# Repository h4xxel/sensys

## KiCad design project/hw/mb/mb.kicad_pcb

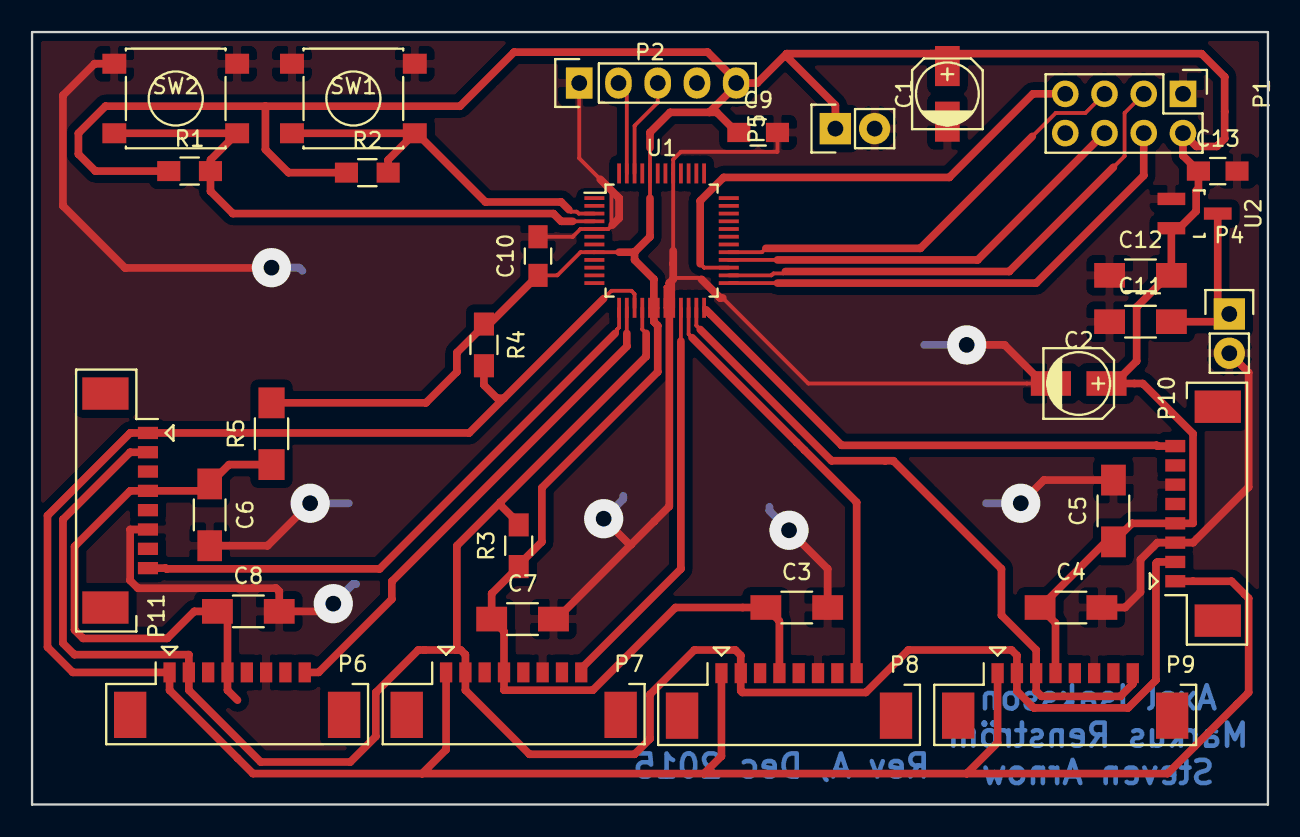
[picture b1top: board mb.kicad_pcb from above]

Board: 2 copper layers, 80.0 x 50.0 mm, 32 parts (0 on the bottom side), 20 nets.

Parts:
C1, C2: CP; c_elec_4x5.7
C3, C4, C5, C6, C7, C8, C11, C12: 1u; C_1206_HandSoldering
C9, C10, C13: 100n; C_0805_HandSoldering
P1: CONN_02X04; Pin_Header_Straight_2x04
P2: CONN_01X05; Pin_Header_Straight_1x05
P4, P5: CONN_01X02; Pin_Header_Straight_1x02
P6, P7, P8, P9, P10, P11: CONN_01X08; Connector_Molex_PicoBlade_53398-0871
R1, R2: R; R_0805_HandSoldering
R3, R4: 4k7; R_0805_HandSoldering
R5: 0; R_1206_HandSoldering
SW1, SW2: SW_PUSH; SW_SPST_PTS645
U1: LPC1114/302; TQFP-48_7x7mm_Pitch0.5mm
U2: mcp1700; SOT-23_Handsoldering

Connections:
+3V3: C1.1, C2.1, C3.1, C4.1, C5.1, C6.1, C7.1, C8.1, C9.1, C10.1, C12.2, C13.1, P1.2, P2.5, P5.1, P6.4, P7.4, P8.4, P9.4, P10.4, P11.4, R1.1, R2.1, R3.1, R4.1, R5.1, R5.2, U1.8, U1.17, U1.18, U1.44, U2.2
/IMUA0: P6.8, U1.14
/IMUA1: P7.8, U1.21
/IMUA2: P8.8, U1.22
/IMUA3: P9.3, P9.8, U1.23
/IMUA4: P10.8, U1.24
/IMUA5: P11.8, U1.13
/MISO: P1.7, U1.27
/MOSI: P1.6, U1.28
/RADIO_CE: P1.3, U1.26
/RADIO_CSN: P1.4, U1.25
/RX: P2.3, U1.46
/SCK: P1.5, U1.29
/SCL: P6.1, P7.1, P8.1, P9.1, P10.1, P11.1, R4.2, U1.15
/SDA: P6.2, P7.2, P8.2, P9.2, P10.2, P11.2, R3.2, U1.16
/TX: P2.2, U1.47
GND: C1.2, C2.2, C3.2, C4.2, C5.2, C6.2, C7.2, C8.2, C9.2, C10.2, C11.1, C12.1, C13.2, P1.1, P2.1, P4.2, P5.2, P6.6, P7.6, P8.6, P9.6, P10.3, P10.6, P11.6, SW1.1, SW2.1, U1.5, U1.19, U1.20, U1.41, U2.1
unnamed: C11.2, P4.1, U2.3
unnamed: R1.2, SW2.2, U1.4
unnamed: R2.2, SW1.2, U1.3

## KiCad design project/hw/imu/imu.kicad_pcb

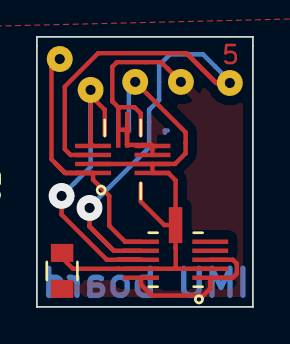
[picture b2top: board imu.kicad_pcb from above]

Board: 2 copper layers, 12.0 x 15.0 mm, 5 parts (1 on the bottom side), 5 nets.

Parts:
C1, C2: 100n; C_0805
P1: CONN_5; Pin_Header_Straight_1x05
U1: LIS2HH12_I2C; LGA4x2
U2: BMG160_i2c; LGA5x1

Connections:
3V3: C1.1, C2.1, P1.3, U1.2, U1.9, U1.10, U2.2, U2.6, U2.10
GND: C1.2, C2.2, P1.4, U1.5, U1.6, U1.7, U1.8, U2.1, U2.3, U2.11
unnamed: P1.1, U1.1, U2.7
unnamed: P1.2, U1.4, U2.9
unnamed: P1.5, U1.3, U2.8

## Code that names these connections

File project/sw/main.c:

#include <stdint.h>
#include "system/LPC11xx.h"
#include "util.h"
#include "uart.h"
#include "main.h"
#include "spi.h"
#include "radiolink.h"
#include "i2c.h"
#include "imu.h"
#include "protocol.h"

#define RANGE IMU_RANGE_HIGHEST

#ifdef DEBUG
#define SAMPLE_FREQ 1
#else
#define SAMPLE_FREQ 50
#endif

uint32_t global_timer;
volatile uint32_t sampleflag = 1;

void initialize(void) {
	/* TODO: Set CPU clock etc. */
	
	LPC_SYSCON->SYSOSCCTRL = 0x3; //Use external oscillator
	LPC_SYSCON->SYSAHBCLKCTRL |= (1 << 16);
	LPC_SYSCON->SYSAHBCLKDIV = 0x1;
	LPC_SYSCON->PDRUNCFG &= ~0x80;
	LPC_SYSCON->SYSPLLCTRL = 0x01;
	LPC_SYSCON->SYSPLLCLKSEL = 0x1; //Use system oscillator and not RC oscillator
	LPC_SYSCON->SYSPLLCLKUEN = 0x0;
	LPC_SYSCON->SYSPLLCLKUEN = 0x1;
	while(!(LPC_SYSCON->SYSPLLSTAT & 1));
	LPC_SYSCON->MAINCLKSEL = 0x3;
	LPC_SYSCON->MAINCLKUEN = 0x1;
	
	/*LPC_IOCON->PIO0_1 &= ~0x7;
	LPC_IOCON->PIO0_1 |= 0x1;
	LPC_SYSCON->CLKOUTDIV = 1;
	LPC_SYSCON->CLKOUTCLKSEL = 0x3;
	LPC_SYSCON->CLKOUTUEN = 0x1;*/
	
	/*********** Enable UART0 **********/
	uart_init();
	
	/********* Enable SPI0 ************/
	spi_init();

	/* Enable timers */
	LPC_SYSCON->SYSAHBCLKDIV |= (1 << 10);
	LPC_SYSCON->SYSAHBCLKDIV |= (1 << 9);
	LPC_SYSCON->SYSAHBCLKCTRL |= (1 << 7);
	
	/*Disable systick*/
	SysTick->CTRL = 0;
	util_delay(100000);
	i2c_init(100);
	//uart_printf("i2c_init() done\n");
	radiolink_init(PROTOCOL_PACKET_SIZE);
	//uart_printf("radiolink_init() done\n");
}

void systick_irq() {
	global_timer++;
	sampleflag = 1;
}

void systick_enable(int frequency) {
	SysTick->LOAD = SYSTEM_CLOCK / frequency;
	SysTick->VAL = 0;
	SysTick->CTRL = 0x1 | 0x2 | 0x4;
}

void setup_pins() {
	LPC_GPIO0->DIR |= (1 << 3); //IMUA0
	LPC_GPIO3->DIR |= (1 << 5); //IMUA1
	LPC_GPIO0->DIR |= (1 << 6); //IMUA2
	LPC_GPIO0->DIR |= (1 << 7); //IMUA3
	LPC_GPIO2->DIR |= (1 << 9); //IMUA4
	LPC_GPIO2->DIR |= (1 << 1); //IMUA5
}

int main(int ram, char **argv) {
	Imu imu[IMU_MAX];
	ProtocolPacket packet[IMU_MAX/2];
	
	uint32_t imus, tmp;
	int i, j;
	
	initialize();
	systick_enable(SAMPLE_FREQ);
	setup_pins();
	
	imus = imu_enumerate();
	
	for(i = 0, tmp = imus; tmp; i++, tmp >>= 1) {
		if(!(tmp & 0x1))
			continue;
		
		debug_printf("Found IMU %i\r\n", i);
		imu_setup(i, RANGE);
	}
	
	debug_printf("IMU setup done\r\n");
	
	unsigned char sync[26] = {
		0xFF, 0xFF, 0xFF, 0xFF, 0xFF, 0xFF, 0xFF, 0xFF, 0xFF, 0xFF, 
		0xFF, 0xFF, 0xFF, 0xFF, 0xFF, 0xFF, 0xFF, 0xFF, 0xFF, 0xFF, 
		0xFF, 0xFF, 0xFF, 0xFF, 0xFF, 0x00, 
	};
	uart_send_raw(sync, PROTOCOL_PACKET_SIZE);
	
	for(;;) {
		protocol_packet_new(packet, RANGE);
		
		if(sampleflag)
			debug_printf("Warning! Missed deadline\r\n");
		while(!sampleflag);
		sampleflag = 0;
		
		debug_printf("-----------------------------------------\r\n");
		for(i = 0, tmp = imus, j = 0; tmp; i++, tmp >>= 1) {
			if(!(tmp & 0x1))
				continue;
			
			imu_sample(i, imu + i);
		
			debug_printf("IMU %i:\r\n\tGyro: x=%hi, y=%hi, z=%hi\r\n\tAccel: x=%hi, y=%hi, z=%hi\r\n",
				i,
				imu[i].gyro.x,
				imu[i].gyro.y,
				imu[i].gyro.z,
				imu[i].accel.x,
				imu[i].accel.y,
				imu[i].accel.z
			);
			
			if(protocol_pack_imu(packet + j, imu + i, i) < 0) {
				j++;
				if(j < IMU_MAX/2)
					protocol_packet_new(packet + j, RANGE);
				protocol_pack_imu(packet + j, imu + i, i);
			}
		}
		
		j = (i + 1)/2;
		
		for(i = 0; i < j; i++) {
			if(!protocol_packet_isempty(packet + i)) {
				debug_printf("Sending packet %i\r\n", i);
				//radiolink_send_stubborn(PROTOCOL_PACKET_SIZE, (void *) (packet + i), 1000);
				uart_send_raw((void *) (packet + i), PROTOCOL_PACKET_SIZE);
			}
		}
	}
	
	return 0;
}

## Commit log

2015-11-06 labb 1
2015-11-20 something
2015-11-20 lab2 works
2015-11-20 bias
2015-11-20 measurments
2015-12-02 slide measurements when timing using computer
2015-12-10 code skeleton
2015-12-10 i2c is working
2015-12-10 hardware
2015-12-10 motherboard cad
2015-12-10 changed csn and ce pins
2015-12-11 imu pcb
2015-12-15 motherboard design done
2015-12-16 arne
2015-12-16 test for imu board
2015-12-17 host computer serial port stuff
2015-12-17 motherboard read gyro
2015-12-17 draw broken crosshair
2015-12-17 get gyro in degrees
2015-12-17 reset message
2015-12-17 crosshair kinda works
2015-12-18 radiolink code that kinda works
2016-01-09 sample IMU data
2016-01-09 Data visualization
2016-01-09 proper sampling code
2016-01-09 Raw data display with angle reset button
2016-01-11 50 MHz
2016-01-11 Started on bone code
2016-01-11 ported gl code to pc
2016-01-11 fixed makefiles
2016-01-11 Started on bones, fixed pigl
2016-01-11 rotate camera
2016-01-11 Maybe possibly that it snaps absolute position to calculated thingomabobs
2016-01-11 vector math madness
2016-01-11 integrating acceleration
2016-01-11 no idea
2016-01-12 added clean exit with esc
2016-01-12 sigint clean exit
2016-01-12 rotate some more..
2016-01-12 oops
2016-01-12 more broken linear algebra
2016-01-12 Broken grid etc
2016-01-12 grid
2016-01-12 this is not gonna work
2016-01-12 added define for global position
2016-01-12 added camera zoom
2016-01-12 Production code?
2016-01-13 draw gravity
2016-01-13 clean up a lot
2016-01-13 more cleanup
2016-01-13 translate lines
2016-01-13 set hgyro
2016-01-13 shotgun maths at work
2016-01-13 draw line color
2016-01-13 print camera pos
2016-01-13 Actually print camera
2016-01-13 set gyro
2016-01-13 Print correct camera values
2016-01-13 reset first imu sample
2016-01-13 Press 'r' to reset radio link
2016-01-13 remove_gravity works
2016-01-13 set gyro working fucking finally
2016-01-13 början
2016-01-13 some code cleanup
2016-01-14 average accelerometers
2016-01-14 Enable bones?
2016-01-14 auto recal gyros
2016-01-14 Malfunctioning global position
2016-01-14 det här pushas
2016-01-15 Everyone hates the radiolinks
2016-01-15 replaced radio with serial for now
2016-01-15 add key to print bone angles
2016-01-16 Wë́'ll mesure stuff and things
2016-01-16 data 1 added
2016-01-16 data2 added
2016-01-16 flowcharts
2016-01-16 removed lock file
2016-01-16 imu schematic, plot scripts
2016-01-16 stupid makefile removing important stuff
2016-01-16 Power usage
2016-01-16 pictures, pictures everywhere
2016-01-17 Skrivit en del och fixat bild på setup
2016-01-17 better description of sensors
2016-01-17 explained the gyro calculation algorithm
2016-01-17 some restructuring
2016-01-17 minor tweak
2016-01-17 Fixat några stavfel och formaterat om lite
2016-01-17 grammar error
2016-01-17 added appendix data
